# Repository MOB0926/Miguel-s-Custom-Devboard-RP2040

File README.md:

# Miguel-s-Custom-Devboard-RP2040
I started this project as a way to practice and learn some more about pcb design. This board is not perfect as it is my second pcb and my first devboard.
    
# Schematic Design
    
I followed the [Custom Devboard Guided Project](https://blueprint.hackclub.com/starter-projects/devboard) by [Kai Pereira](https://github.com/KaiPereira/build-a-devboard) so it was not my design but I did rout the PCB myself an added and LED.
     
The designs and components are directly from the guide but the LED I added once I realized how empty the board was at the pcb design section.
    
Components:
- RP 2040
- LED (SK6812-mini-e)   This is not in KICAD lib, I had to use [Master Lib](https://github.com/ebastler/marbastlib)
- USB-C-2.0
- Voltage regulator (MCP1700T-3302E/TT)
- Crystal Ocilater (12mhz)
- I/O (1x20)x2 (1x3)x1
- Flash Memory/Storage (W25Q16JVZPIQ) (16-Mbi)

# PCB Design
     
The board dimensions and I/O location are exact from the guide but the rest I ended up moving around to fit my routing. The LED I placed in the very empty bottom of the board above the 1x3 pins.
         
I routed the USB first then the Flash, followed by the crystal ocilator. Once the important connections were made I connected the I/O and LED, lastly I set up the ground pour and fixed any errors the ERC flaged.

# Prep For Manufacturing
         
Once I was sure I had finished the board I downloaded the necessary design files from KICAD (.gbr , BOM , CPL) I edited the BOM and CPL formats to fit JLCPCB and uploaded my design.
      
Once the files were uploaded, I chose the correct settings for my design and whent on to choosing what parts JLCPCB would buy and install for me.
          
ALL basic components I selected and most Extended components as they are far to complicated to solder myself but the I/O pins and LED I will add myself to save A LOT of money. (Almost 30 dollars)
      
I actually made an error originaly where my board was set up as "Standard PCBA" not "Economic PCBA" which is why I had to place the LED myself and why I saved $30.

# V1 vs V2
          
Honestly they are not too different but V2 was a complete restart for the pcb routing and component placement as V1 was full of errors that were easier to re-do than fix.
       
# BOM
    
- PCB ~ $39.36 [JLCPCB](https://jlcpcb.com/) (For 5 pcbs / 2 pcba)
- I/O Pins ~ $1.26 + Shipping [AliExpress](https://www.aliexpress.us/item/3256805070463808.html?spm=a2g0o.cart.0.0.7e6b38daz93qME&mp=1&pdp_npi=6%40dis%21USD%21USD%201.26%21USD%201.26%21%21USD%201.26%21%21%21%4021032f3717684542606396685e305a%2112000032382468616%21ct%21US%216785194544%21%211%210%21&gatewayAdapt=glo2usa) (For 10 1x40 Breakeable 2.54mm Male Pins)
- LED (SK6812mini-e)(3mA) ~ $3.51 + Shipping [AliExpress]([https://www.aliexpress.us/item/3256806781745425.html?spm=a2g0o.productlist.main.2.30f32c52NpVRiA&algo_pvid=19ea0063-2bd2-4e94-b170-fb60ab4e0a6e&algo_exp_id=19ea0063-2bd2-4e94-b170-fb60ab4e0a6e-1&pdp_ext_f=%7B%22order%22%3A%226%22%2C%22eval%22%3A%221%22%2C%22fromPage%22%3A%22search%22%7D&pdp_npi=6%40dis%21USD%212.23%212.23%21%21%2115.48%2115.48%21%40210328db17680140383654328ef58e%2112000038888086591%21sea%21US%210%21ABX%211%210%21n_tag%3A-29910%3Bd%3Ac04e790%3Bm03_new_user%3A-29895&curPageLogUid=fUqIvQ2YwTf7&utparam-url=scene%3Asearch%7Cquery_from%3A%7Cx_object_id%3A1005006968060177%7C_p_origin_prod%3A](https://www.aliexpress.us/item/3256807677321116.html?spm=a2g0o.cart.0.0.4a2b38daTsU0eW&mp=1&pdp_npi=6%40dis%21USD%21USD%203.51%21USD%203.51%21%21USD%203.51%21%21%21%40210318a717684412643941390e3c3f%2112000042594617264%21ct%21US%216785194544%21%211%210%21&gatewayAdapt=glo2usa)) (For 100) (Only need one but this is cheaper because of choice shipping than getting a 10pc)
- Total ~ $47
    
# THE END
     
So yeah thats it really
    
I spent about 19-20 hours on this. I learnt A LOT about Schematic/PCB design on KICAD specificaly. I also learnt how to get a project to manufacturing (Which I cant wait to get my first Devboard design to play with)
     
I do not plan to return to this project, I will probably at some point in the near future make another board but with a more specific use and maybe a diferent MCU so I can get more experience

# Thanks

- Myself (For all the time I put into this)
- [Kai Pereira](https://kaipereira.com/) (For the Guide)
- [HackClub](https://hackclub.com/) / [Blueprint](https://blueprint.hackclub.com/home) (For the opportunity to do a project like this)
- You (For reading this)

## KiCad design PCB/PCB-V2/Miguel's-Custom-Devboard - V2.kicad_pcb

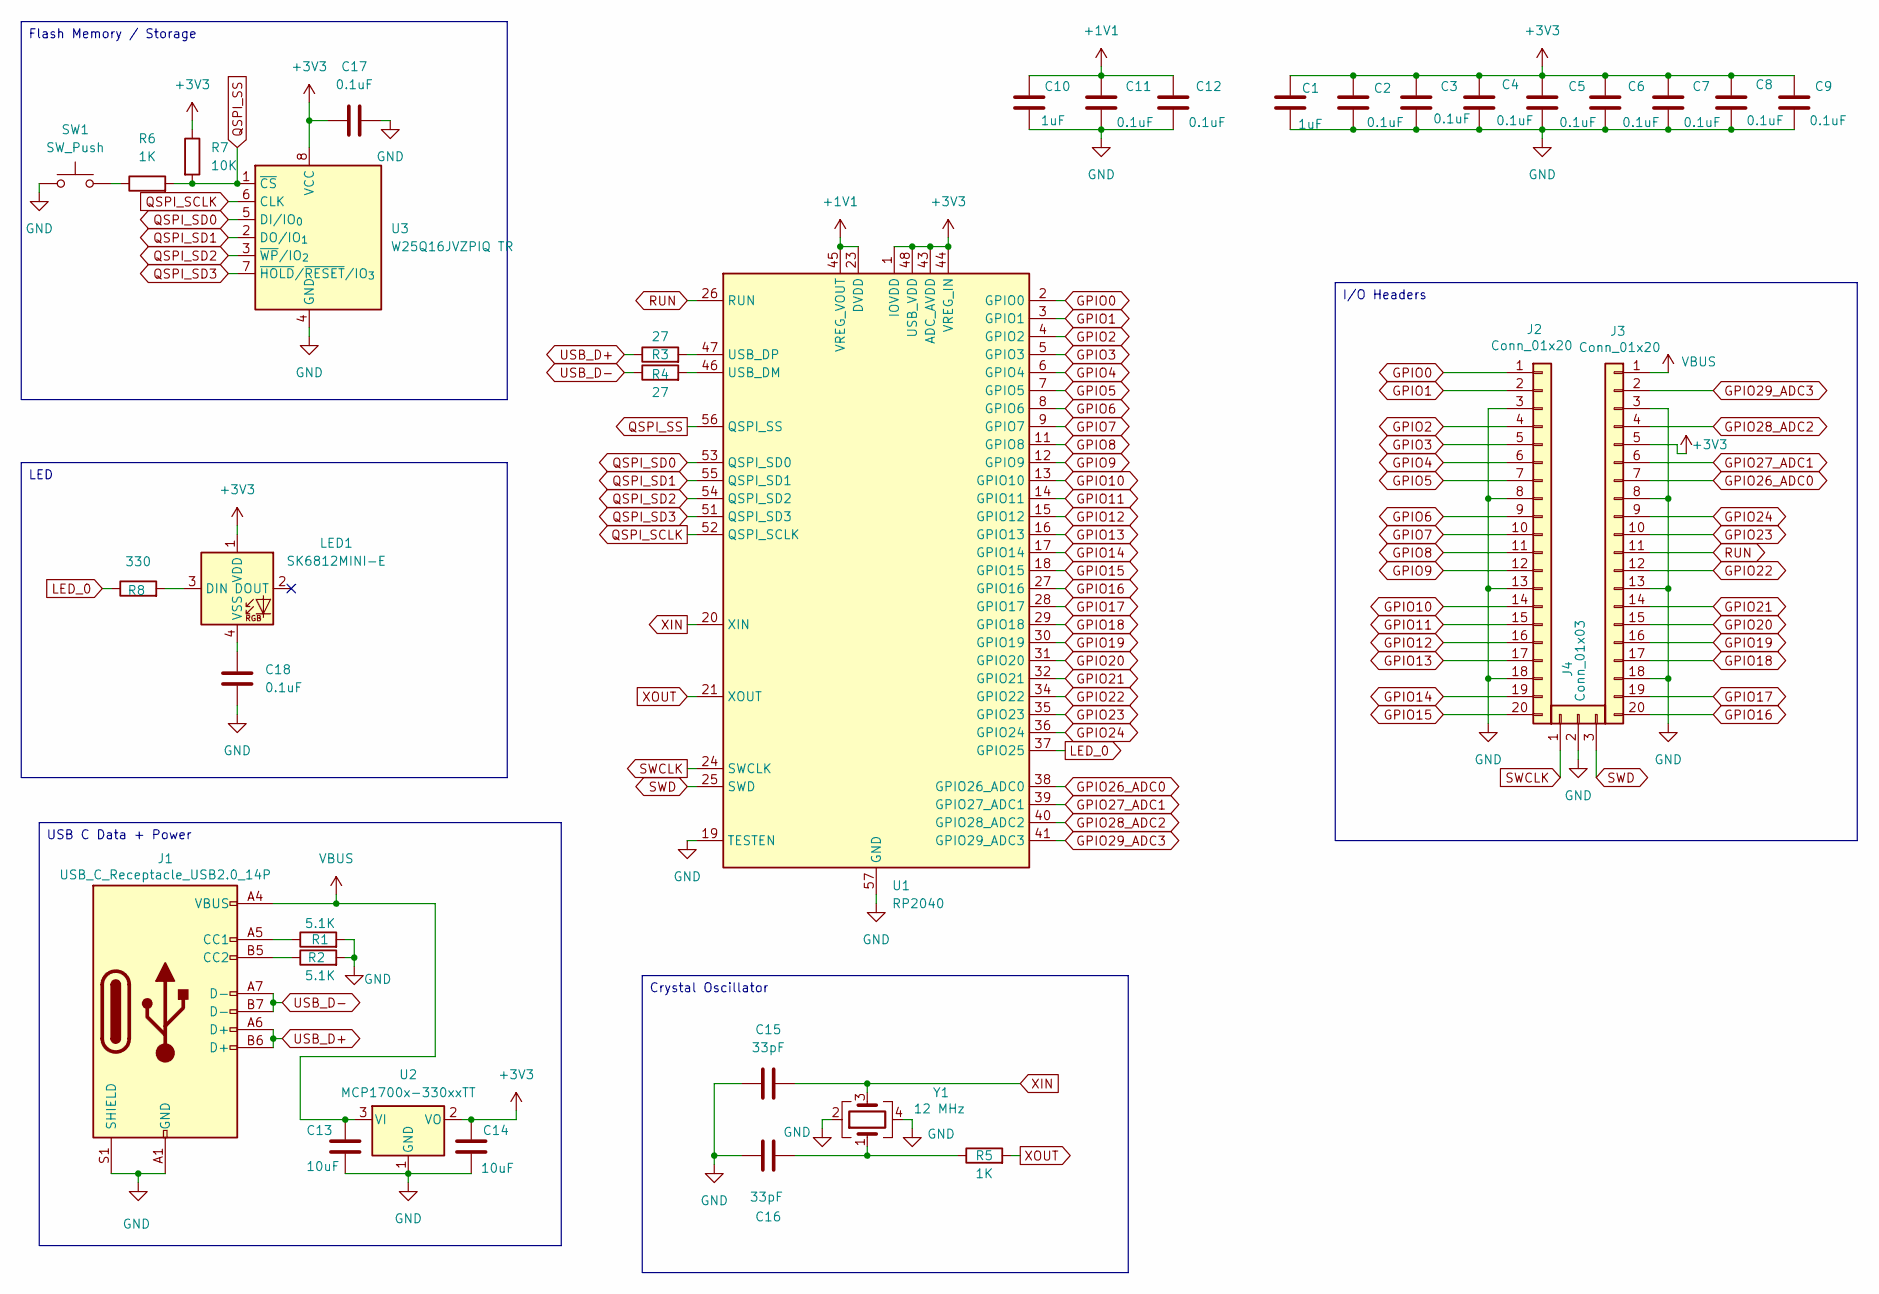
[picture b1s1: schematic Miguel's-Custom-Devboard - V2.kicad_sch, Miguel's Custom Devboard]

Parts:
C1, C10: 1uF; C_0402_1005Metric
C2, C3, C4, C5, C6, C7, C8, C9, C11, C12, C17, C18: 0.1uF; C_0402_1005Metric
C13, C14: 10uF; C_0603_1608Metric
C15, C16: 33pF; C_0402_1005Metric
J1: USB_C_Receptacle_USB2.0_14P; USB_C_Receptacle_HRO_TYPE-C-31-M-12
J2, J3: Conn_01x20; PinHeader_1x20_P2.54mm_Vertical
J4: Conn_01x03; PinHeader_1x03_P2.54mm_Vertical
LED1: SK6812MINI-E; LED_6028R
R1, R2: 5.1K; R_0402_1005Metric
R3, R4: 27; R_0402_1005Metric
R5, R6: 1K; R_0402_1005Metric
R7: 10K; R_0402_1005Metric
R8: 330; R_0402_1005Metric
SW1: SW_Push; SW_Push_SPST_NO_Alps_SKRK
U1: RP2040; QFN-56-1EP_7x7mm_P0.4mm_EP3.2x3.2mm
U2: MCP1700x-330xxTT; SOT-23
U3: W25Q16JVZPIQ TR; Winbond_USON-8-1EP_3x2mm_P0.5mm_EP0.2x1.6mm
Y1: 12 MHz; Crystal_SMD_3225-4Pin_3.2x2.5mm

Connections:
+1V1: C10.1, C11.1, C12.1, U1.23 (DVDD), U1.45 (VREG_VOUT), U1.50 (DVDD)
+3V3: C1.1, C2.1, C3.1, C4.1, C5.1, C6.1, C7.1, C8.1, C9.1, C14.1, C17.1, J3.5, LED1.1 (VDD), R7.1, U1.1 (IOVDD), U1.10 (IOVDD), U1.22 (IOVDD), U1.33 (IOVDD), U1.42 (IOVDD), U1.43 (ADC_AVDD), U1.44 (VREG_IN), U1.48 (USB_VDD), U1.49 (IOVDD), U2.2 (VO), U3.8 (VCC)
GND: C1.2, C2.2, C3.2, C4.2, C5.2, C6.2, C7.2, C8.2, C9.2, C10.2, C11.2, C12.2, C13.2, C14.2, C15.1, C16.1, C17.2, C18.2, J1.A1 (GND), J1.A12 (GND), J1.B1 (GND), J1.B12 (GND), J1.S1 (SHIELD), J2.3, J2.8, J2.13, J2.18, J3.3, J3.8, J3.13, J3.18, J4.2, R1.2, R2.2, SW1.1, U1.19 (TESTEN), U1.57 (GND), U2.1 (GND), U3.4 (GND), Y1.2, Y1.4
GPIO0: J2.1, U1.2 (GPIO0)
GPIO1: J2.2, U1.3 (GPIO1)
GPIO2: J2.4, U1.4 (GPIO2)
GPIO3: J2.5, U1.5 (GPIO3)
GPIO4: J2.6, U1.6 (GPIO4)
GPIO5: J2.7, U1.7 (GPIO5)
GPIO6: J2.9, U1.8 (GPIO6)
GPIO7: J2.10, U1.9 (GPIO7)
GPIO8: J2.11, U1.11 (GPIO8)
GPIO9: J2.12, U1.12 (GPIO9)
GPIO10: J2.14, U1.13 (GPIO10)
GPIO11: J2.15, U1.14 (GPIO11)
GPIO12: J2.16, U1.15 (GPIO12)
GPIO13: J2.17, U1.16 (GPIO13)
GPIO14: J2.19, U1.17 (GPIO14)
GPIO15: J2.20, U1.18 (GPIO15)
GPIO16: J3.20, U1.27 (GPIO16)
GPIO17: J3.19, U1.28 (GPIO17)
GPIO18: J3.17, U1.29 (GPIO18)
GPIO19: J3.16, U1.30 (GPIO19)
GPIO20: J3.15, U1.31 (GPIO20)
GPIO21: J3.14, U1.32 (GPIO21)
GPIO22: J3.12, U1.34 (GPIO22)
GPIO23: J3.10, U1.35 (GPIO23)
GPIO24: J3.9, U1.36 (GPIO24)
GPIO26_ADC0: J3.7, U1.38 (GPIO26_ADC0)
GPIO27_ADC1: J3.6, U1.39 (GPIO27_ADC1)
GPIO28_ADC2: J3.4, U1.40 (GPIO28_ADC2)
GPIO29_ADC3: J3.2, U1.41 (GPIO29_ADC3)
LED_0: R8.1, U1.37 (GPIO25)
unnamed: C16.2, R5.1, Y1.1
unnamed: J1.A5 (CC1), R1.1
unnamed: J1.B5 (CC2), R2.1
unnamed: LED1.3 (DIN), R8.2
unnamed: C18.1, LED1.4 (VSS)
unnamed: R6.1, SW1.2
unnamed: R4.2, U1.46 (USB_DM)
unnamed: R3.2, U1.47 (USB_DP)
QSPI_SCLK: U1.52 (QSPI_SCLK), U3.6 (CLK)
QSPI_SD0: U1.53 (QSPI_SD0), U3.5 (DI/IO_{0})
QSPI_SD1: U1.55 (QSPI_SD1), U3.2 (DO/IO_{1})
QSPI_SD2: U1.54 (QSPI_SD2), U3.3 (~WP/IO_{2})
QSPI_SD3: U1.51 (QSPI_SD3), U3.7 (~HOLD/~RESET/IO_{3})
QSPI_SS: R6.2, R7.2, U1.56 (QSPI_SS), U3.1 (~CS)
RUN: J3.11, U1.26 (RUN)
SWCLK: J4.1, U1.24 (SWCLK)
SWD: J4.3, U1.25 (SWD)
USB_D+: J1.A6 (D+), J1.B6 (D+), R3.1
USB_D-: J1.A7 (D-), J1.B7 (D-), R4.1
VBUS: C13.1, J1.A4 (VBUS), J1.A9 (VBUS), J1.B4 (VBUS), J1.B9 (VBUS), J3.1, U2.3 (VI)
XIN: C15.2, U1.20 (XIN), Y1.3
XOUT: R5.2, U1.21 (XOUT)

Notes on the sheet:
Crystal Oscillator
Flash Memory / Storage
I/O Headers
USB C Data + Power
LED

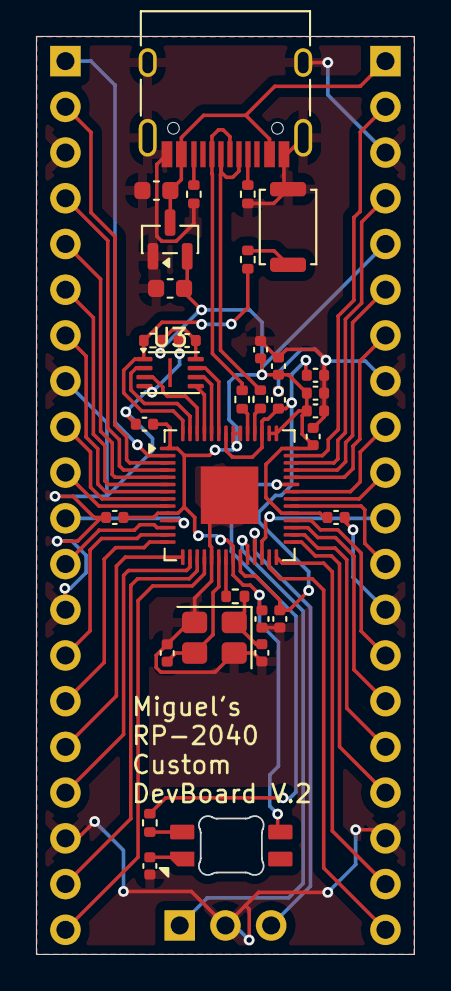
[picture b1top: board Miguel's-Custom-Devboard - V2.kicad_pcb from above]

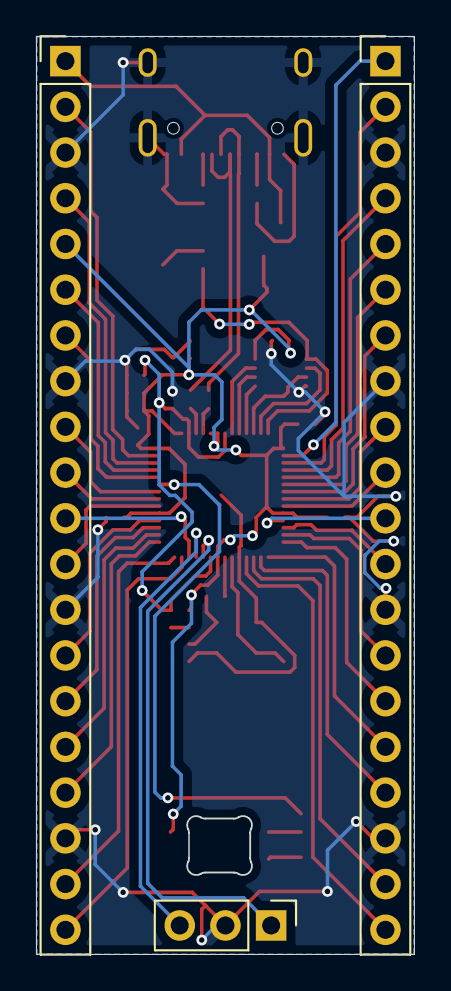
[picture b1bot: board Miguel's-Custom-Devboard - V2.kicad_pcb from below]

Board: 2 copper layers, 20.9 x 51.0 mm, 36 parts (3 on the bottom side), 55 nets.

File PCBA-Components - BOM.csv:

Comment,Designator,Footprint,JLCPCB Part #
330,R8,R_0402_1005Metric,C25104
1uF,"C1,C10",C_0402_1005Metric,C52923
MCP1700x-330xxTT,U2,SOT-23,C39051
33pF,"C15,C16",C_0402_1005Metric,C1562
1K,"R6,R5",R_0402_1005Metric,C11702
5.1K,"R1,R2",R_0402_1005Metric,C25905
12MHz,Y1,Crystal_SMD_3225-4Pin_3.2x2.5mm,C9002
10uF,"C14,C13",C_0603_1608Metric,C19702
RP2040,U1,QFN-56-1EP_7x7mm_P0.4mm_EP3.2x3.2mm,C2040
0.1uF,"C17,C7,C8,C2,C12,C9,C11,C5,C3,C4,C6,C18",C_0402_1005Metric,C1525
W25Q16JVZPIQTR,U3,Winbond_USON-8-1EP_3x2mm_P0.5mm_EP0.2x1.6mm,C2843335
10K,R7,R_0402_1005Metric,C25744
USB_C_Receptacle_USB2.0_14P,J1,USB_C_Receptacle_HRO_TYPE-C-31-M-12,C165948
27,"R3,R4",R_0402_1005Metric,C25100
SW_Push,SW1,SW_Push_SPST_NO_Alps_SKRK,C720477

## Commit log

2026-01-08 LED Change (Files Updated)
2026-01-10 Update README with manufacturing prep details
    Added images and detailed the prep process for manufacturing.
2026-01-10 Remove duplicate LED entry from BOM section
2026-01-10 3-D picture
2026-01-10 Last was wrong
2026-01-10 Revise component prices and shipping details
    Updated pricing and links for components in the README.
2026-01-10 Adjust total cost estimate in README
    Updated total cost estimate in the README.
2026-01-15 Revise BOM prices and links for components
    Updated prices and links for I/O Pins and LED components in the BOM section.
2026-03-15 Final Update
